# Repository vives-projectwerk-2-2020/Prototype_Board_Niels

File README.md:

# Prototype board with sensors

## Description

In this readme you can find all information about the prototype board with sensors. I made first a test board this board cannot be placed inside the box. This board works perfect with all sensors. The second board i made is made to put inside the box, i also implemented extra pins for the other boards. I also added a extra part to get the SDS011 sensor in sleep mode i will explain this in the info below.

## The nucleo

The central part of my board is the nucleo-L432KC. The STM32 Nucleo-32 board provides an affordable and flexible way for users to try out new concepts and build prototypes with the STM32 microcontroller, choosing from the various combinations of performance, power consumption and features. In the picture below you can see how the nucleo looks like and how the pins are devided. If i talk about pins in the info beneeth you can look on this picture where you can find the pins.

## Shematic of the old board

In this shematic you see in the center of the shematic 2 big blocks the top one is the left side of the nucleo-L432KC. The block below is the right side of the nucleo-L432KC. On the right side from the second nucleo-L432KC block you can see 2 pins they are called JP2 and JP3. These pins were provided for the solar panel board, JP2 is connected with the Vin from the nucleo and JP3 is just the ground. There is also a reset button connected to NRST on the nucleo.

Right below the pins JP2 and JP3 you can see one big connector, this is the connector for connecting the LoRaWAN-antenna board. Pins 1, 8, 9 are connected to the ground, pin 12 is connected with the 3V3 and a capacitor with a value of 100 nF.
Pins 7, 10, 11, 15 are not connected, pin 2 is connected to pin D12 on the nucleo. Pin 3 is connected with D11 on the nucleo, pin 4 is connected with D13 on the nucleo, pin 5 is connected with D0 on the nucleo. Pin 6 is connected with a resistor with a value of 4k7 ohm, this pin is also connected with D1 on the nucleo. Pin 13 is connected with D2 on the nucleo, pin 14 is connected with D3 on the nucleo.

Left from the top block from the nulceo you can see a connector that is called SDS011. This connector has pins so that you connect the SDS011 sensor on it. You can see that pin 1 is not connected this is because the connector from the SDS011 has 5 pins and one is not connected. Pin 2 is connected to 3v3 but this has been changed in the newer shematic because the sensor has to work on 5V, pin 3 is connected to the ground. Pin 4 is connected to D1 on the nucleo and Pin 5 is connected to D0 on the nucleo.

Right from the top block from the nulceo you can see a connector that is called BME280. This connector has female pins so you can put the BME280 sensor on it. Pin 2 is not connected, Pin 1 and 7 are connected to 3V3 and pin 3 and 5 are connected to the ground. Pin 4 is connected to D5 on the nucleo and pin 6 is connected to D4 on the nucleo.

On top of the shematic you can see a big block this is the EEPROM. Pin 2 is connected to the ground and pin 4 is connected to the VCC. Pin 5 is not connected, pin 1 is connected to a resistor with a value of 2k2 ohm to protect the SCL line and is connected tot the D5 on the nucleo. Pin 3 is connected to a resistor with a value of 2k2 ohm to protect the SDA line and is connected with D4 on the nucleo.

## Block diagram old board

Here can you see the block diagram of the old board. This block diagram is a quick summary of what is on my old board.

## Board shematic of the old board

On the top of the board you can see 4 holes this is the VCC of the SDS011 sensor. These holes are were provided so you could erase the line and add more voltage to it from the solar pannel board. These holes were removed on the newest board.

## The print when nothing was soldered

## The print when everything is soldered

## Testing the SDS011 sensor

1. Setup of the sensor.

2. Reading the values in putty.

3. Extra information.
    * The pins are connected on D0 and D1.

## Testing the EEPROM driver

1. Setup of the sensor.

2. Reading out an array in putty.

3. Extra information.
    * While testing i connected the pins to D4 and D5.

## Testing the BME280 sensor

I could not test this sensor because i don't have that sensor at home. I tested it with the fake values from Ladzlo and something was wrong with compiling. But other people tried this sensor and connected it just like how i connected it in my shematic so normally it would work perfectly.

1. Setup of the sensor.

   Connect the sensor in the pins in the red circle shown in the picture below.

2. Extra information.
    * I connected the BME to pins D4 and D5 on the nucleo.

## Testing antenna PCB board

This test has been executed by Laura this pcb works perfectly together with my board all the info about the tests can you find in the github repository from the antenna board.

1. Setup of the boards.

2. Extra information.
    * You can find extra information in the link below.
    * [Link testing LoRaWAN-antenna](https://github.com/vives-projectwerk-2-2020/LoRaWAN-antenna)

## Shematic of the new board

The difference between the old and the new board is that i added extra pins for the battery pcb and also pins for an extra board so that the voltage can go from 3V3 to 5V so that the SDS011 sensor can work well. I also added sleep mode for the SDS011.

Left from the lowest nucleo shematic i added added 3 extra connectors. SV3 is provided so that the solar board can be connected to my board. SV2 are connectors to add the extra print that converts te voltage 3V3 to 5V, we have to do that so that the SDS011 can function well.

Below the SV2 connector there are 2 pins these pins are provided to connect the wires from the batteries to my pcb. In the board you can also see a lot of holes. These holes are provided to connect the pcb with the box, the 2 holes in the center are provided for the batteries you can connect these under the PCB or above.

In the top left of the shematic you can see i added there also extra components. These components are provided so that the SDS011 can go in sleep mode. I connected this to pin D2 on the nucleo, the info about the shematic can you find in the topic "Adding components to the old board so that the SDS011 sensor can go in sleep mode" this will be discussed below.

## Adding components to the old board so that the SDS011 sensor can go in sleep mode

I upgraded the old shematic a bit so that the SDS011 sensor can go in sleep mode. In the picture below you can see the shematic about how to make it.

When the digital output goes high, Q1 is turned on. That pulls down the gate of Q2 low, turning it on.
When the digital output is low, Q1 is held off. R1 then pulls the gate high, turning off Q2.
R1 was chosen to be so high to minimize the current when the device is powered on.

## Block diagram new board

Here can you see the block diagram of the new board. This block diagram is a quick summary of what is on my new board.

## Board shematic of the new board

## The waterproof box

All the boards from the hardware needs to be combined in this waterproof box. In the picture below you can see how we arranged the prints in the box. The grey sensor board is my board, all the other boards will be connected to my board with connectors or with holes in the pcb. I can connect also my pcb to the box. You can see in the picture that the antenna board is far away from the other pcb's. This is because the antenna may not get malfunctions from other boards. The part that is not on the picture but in the box are the batteries. You can add the batteries under my print or add it on top of it with spacers.

## Partlist

* [Female header](https://be.farnell.com/samtec/ssw-107-01-t-s/connector-rcpt-7pos-1row-2-54mm/dp/2667434)
* [Pinheader SDS011](https://be.farnell.com/molex/22-28-4050/connector-header-5pos-1row-2-54mm/dp/2381173)
* [Push button](https://be.farnell.com/c-k-components/pts645sl43-2-lfs/tactile-switch-spst-0-05a-12vdc/dp/2435161)
* [EEPROM](https://be.farnell.com/microchip/24aa64t-i-ot/serial-eeprom-64kbit-400khz-sot/dp/2101260)
* [100 nF capacitor](https://be.farnell.com/avx/02016d104kat2a/cap-0-1-f-6-3v-10-x5r-0201/dp/1657913?st=smd%20capacitor)
* [2k2 ohm resistor](https://be.farnell.com/vishay/crcw06032k20fkeahp/res-2k2-1-0-33w-0603-thick-film/dp/1738909?st=2k2%20smd%20resistor)
* [100k ohm resistor](https://be.farnell.com/vishay/crcw0402100kfked/res-100k-1-0-063w-0402-thick-film/dp/1469671?st=100k%20smd%20resistor)
* [1M ohm resistor](https://be.farnell.com/vishay/crcw04021m00fked/res-1m-1-0-063w-0402-thick-film/dp/1469667?st=1M%20smd%20resistor)
* [4k7 ohm resistor](https://be.farnell.com/vishay/crcw06034k70fkea/res-4k7-1-0-1w-0603-thick-film/dp/1469807?st=4k7%20smd%20resistor)
* [15 pins Female header](https://be.farnell.com/harwin/m20-7821546/connector-rcpt-15pos-2-54mm-1row/dp/3225931)
* [4 pins Female header](https://be.farnell.com/multicomp/2212s-04sg-85/socket-pcb-1-row-4way/dp/1593460)
* [5 pins Female header](https://be.farnell.com/multicomp/2212s-05sg-85/socket-pcb-1-row-5way/dp/1593461)
* [2 pins Male header](https://be.farnell.com/amp-te-connectivity/5-146281-2/board-board-connector-header-2/dp/1792060)
* [Nucleo](https://be.farnell.com/stmicroelectronics/nucleo-l432kc/dev-board-nucleo-32/dp/2580786?scope=partnumberlookahead&ost=NUCLEO-L432KC&searchref=searchlookahead&exaMfpn=true&ddkey=https%3Anl-BE%2FElement14_Belgium%2Fw%2Fsearch)
* [Transistor](https://be.farnell.com/on-semiconductor/mmbt4401lt1g/transistor-npn-sot-23/dp/1459105?st=MMBT4401)
* [Mosfet](https://be.farnell.com/on-semiconductor/ntr4101pt1g/mosfet-p-20v-sot-23/dp/1431303?st=NTR4101PT1G%20P-Channel%20MOSFET)

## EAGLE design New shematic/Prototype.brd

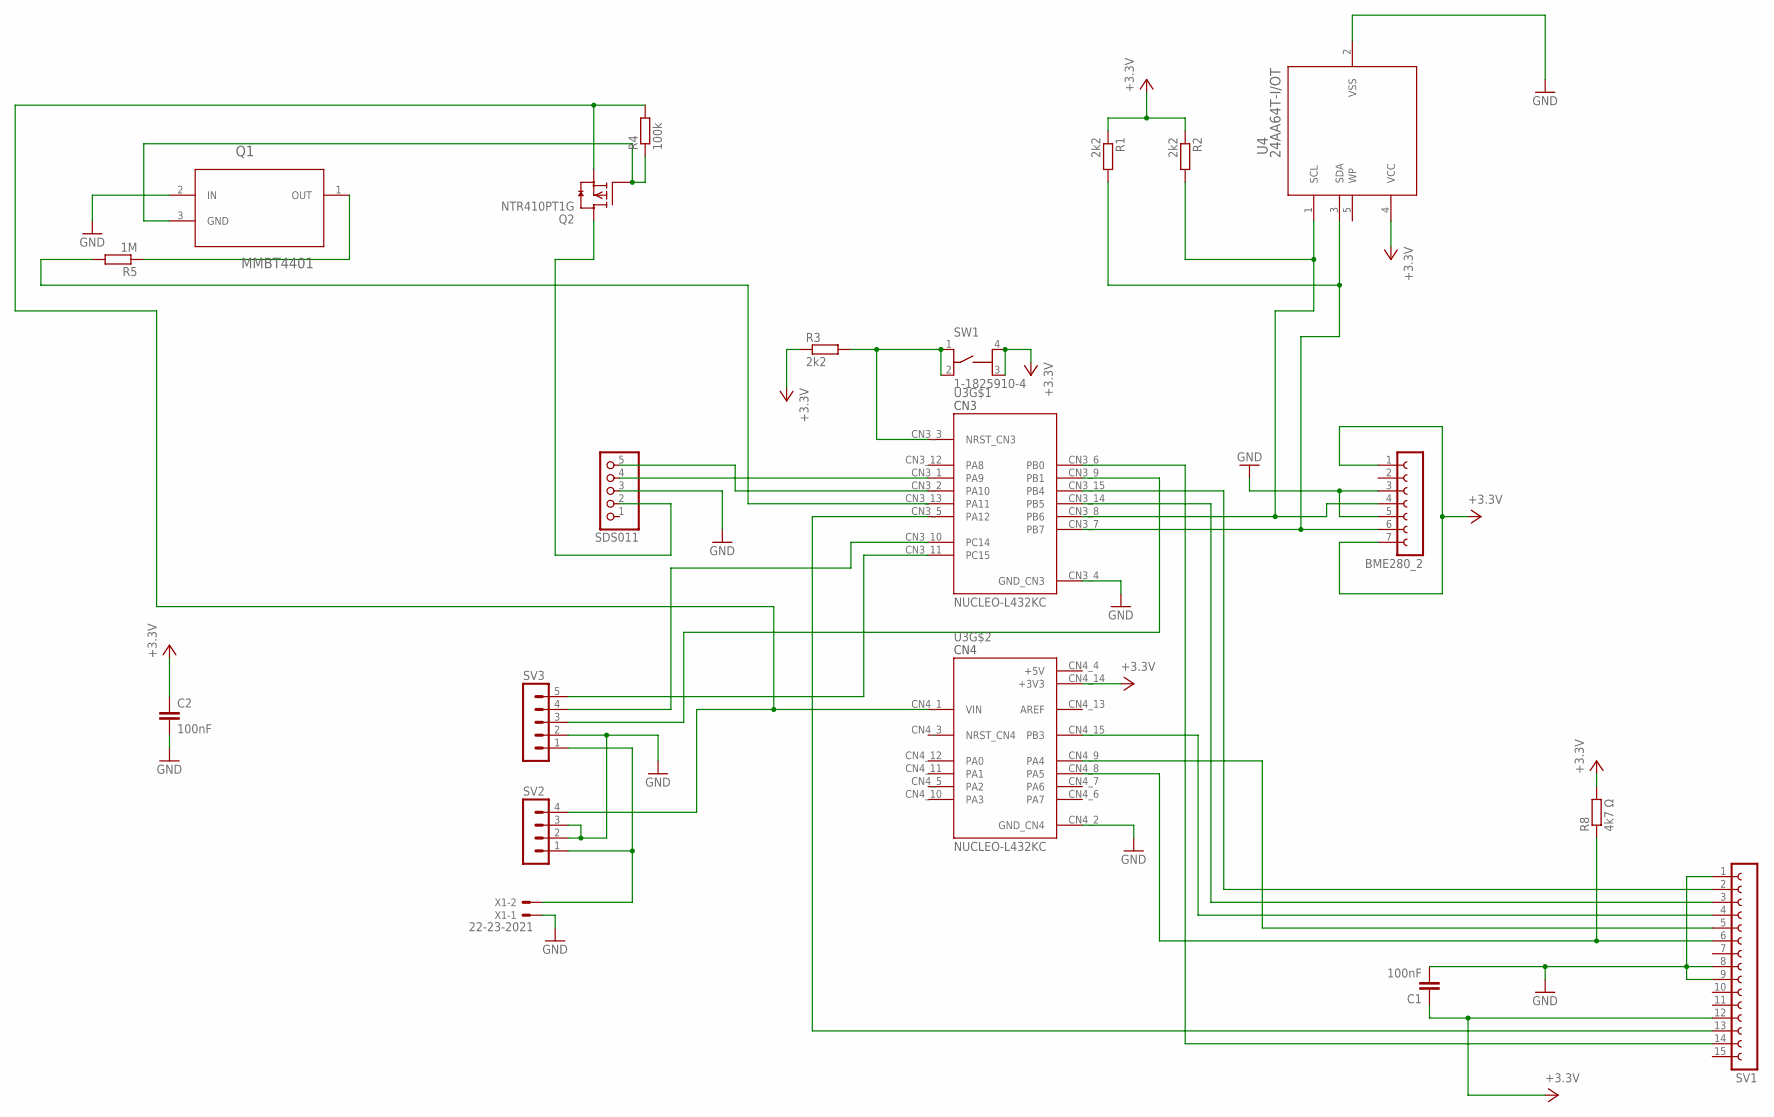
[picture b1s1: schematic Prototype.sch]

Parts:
BME280_2: FE07-1; FE07
C1, C2: 100nF; C0603K
Q1: MMBT4401; SOT95P263X110-3N
Q2: NTR410PT1G; SOT23
R1, R2, R3: 2k2; R1206W
R4: 100k; R1206W
R5: 1M; R1206W
R8: 4k7 Ω; R1206W
SDS011: PINHD-1X5; 1X05
SV1: FE15-1; FE15
SV2: MA04-1
SV3: MA05-1
SW1: 1-1825910-4; TE_1-1825910-4
U3: NUCLEO-L432KC; MODULE_NUCLEO-L432KC
U4: 24AA64T-I/OT; SOT-23-5_MC
X1: 22-23-2021

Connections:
+5V: U3.CN4_4 (+5V)
GND: BME280_2.3, BME280_2.5, C1.2, C2.2, Q1.2 (IN), SDS011.3, SV1.1, SV1.8, SV1.9, SV2.2, SV2.3, SV3.2, U3.CN3_4 (GND_CN3), U3.CN4_2 (GND_CN4), U4.2 (VSS), X1.1
unnamed: SV1.5, U3.CN4_9 (PA4)
unnamed: SDS011.4, U3.CN3_1 (PA9)
unnamed: SV1.14, U3.CN3_6 (PB0)
unnamed: BME280_2.4, R2.2, U3.CN3_8 (PB6), U4.1 (SCL)
unnamed: R3.2, SW1.1, SW1.2, U3.CN3_3 (NRST_CN3)
unnamed: SDS011.5, U3.CN3_2 (PA10)
unnamed: Q1.3 (GND), Q2.1 (G), R4.1
unnamed: Q2.3 (D), SDS011.2
unnamed: SV1.13, U3.CN3_5 (PA12)
unnamed: R8.1, SV1.6, U3.CN4_8 (PA5)
unnamed: SV1.3, U3.CN3_14 (PB5)
unnamed: Q2.2 (S), R4.2, SV2.4, U3.CN4_1 (VIN)
unnamed: SV1.2, U3.CN3_15 (PB4)
unnamed: SV1.4, U3.CN4_15 (PB3)
unnamed: Q1.1 (OUT), R5.1
unnamed: SV2.1, SV3.1, X1.2
unnamed: BME280_2.6, R1.2, U3.CN3_7 (PB7), U4.3 (SDA)
unnamed: SV3.3, U3.CN3_9 (PB1)
unnamed: SV3.4, U3.CN3_10 (PC14)
unnamed: SV3.5, U3.CN3_11 (PC15)
unnamed: R5.2, U3.CN3_13 (PA11)
VCC: BME280_2.1, BME280_2.7, C1.1, C2.1, R1.1, R2.1, R3.1, R8.2, SV1.12, SW1.3, SW1.4, U3.CN4_14 (+3V3), U4.4 (VCC)

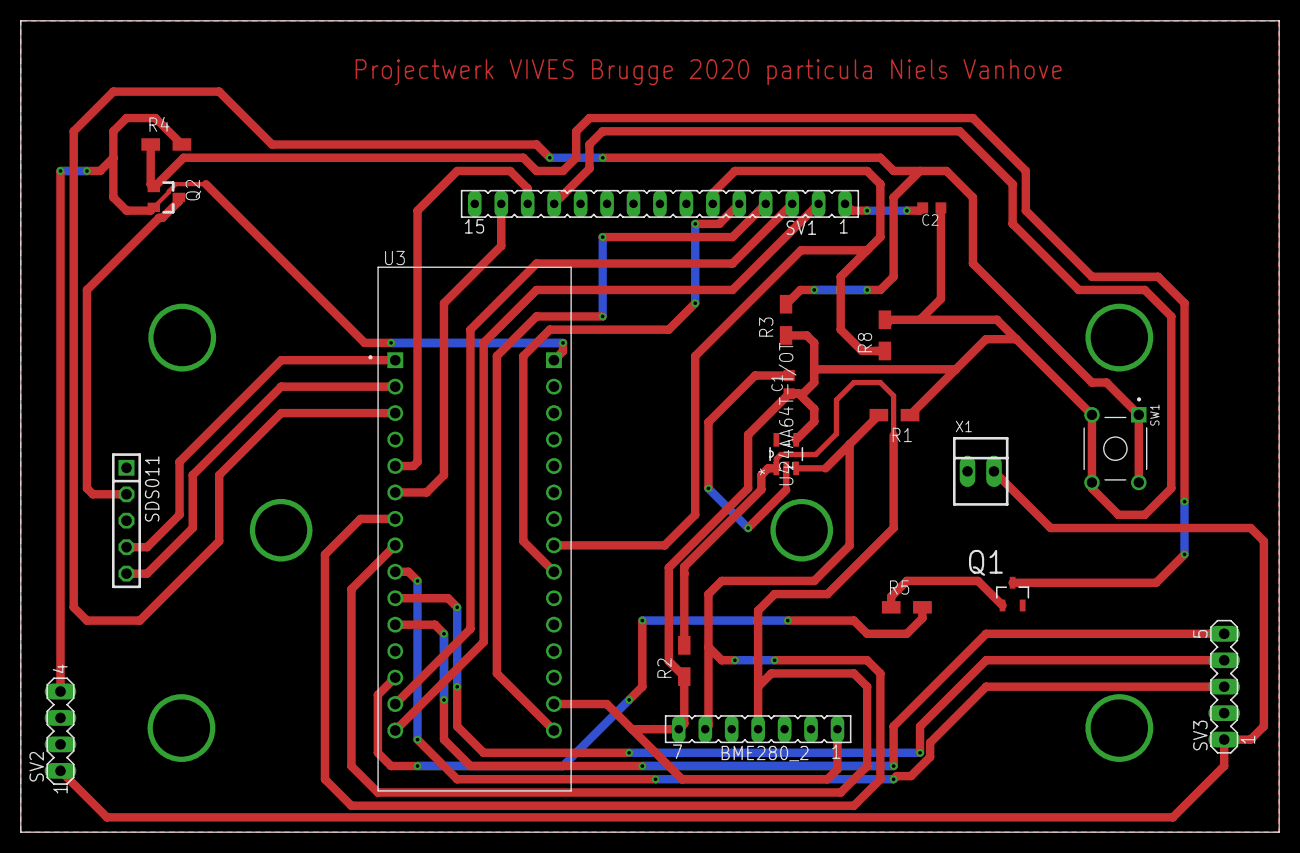
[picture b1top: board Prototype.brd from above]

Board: 2 copper layers, 120.8 x 77.9 mm, 19 parts (0 on the bottom side), 23 nets.

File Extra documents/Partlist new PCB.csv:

Part;Value;Device;Package;Description;Links
BME280_2;;FE07-1;FE07;FEMALE HEADER;https://be.farnell.com/samtec/ssw-107-01-t-s/connector-rcpt-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
C1;100nF;C-EUC0603K;C0603K;CAPACITOR, European symbol;https://be.farnell.com/avx/02016d104kat2a/cap-0-1-f-6-3v-10-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
C2;100nF;C-EUC0603K;C0603K;CAPACITOR, European symbol;https://be.farnell.com/avx/02016d104kat2a/cap-0-1-f-6-3v-10-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
Q1;MMBT4401;LM3480IM3-5.0;SOT95P263X110-3N;Linear Voltage Regulator;https://be.farnell.com/on-semiconductor/mmbt4401lt1g/transis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
Q2;NTR410PT1G;BSS84LT1;SOT23;OnSemi's BSS84LT1 Power MOSFET 130 mA, 50 V RDS(on) = 10;https://be.farnell.com/on-semiconductor/ntr4101pt1g/mosfet-p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
R1;2k2;R-EU_R1206W;R1206W;RESISTOR, European symbol;https://be.farnell.com/vishay/crcw06032k20fkeahp/res-2k2-1-0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
R2;2k2;R-EU_R1206W;R1206W;RESISTOR, European symbol;https://be.farnell.com/vishay/crcw06032k20fkeahp/res-2k2-1-0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
R3;2k2;R-EU_R1206W;R1206W;RESISTOR, European symbol;https://be.farnell.com/vishay/crcw06032k20fkeahp/res-2k2-1-0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
R4;100k;R-EU_R1206W;R1206W;RESISTOR, European symbol;https://be.farnell.com/vishay/crcw0402100kfked/res-100k-1-0-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
R5;1M;R-EU_R1206W;R1206W;RESISTOR, European symbol;https://be.farnell.com/vishay/crcw04021m00fked/res-1m-1-0-06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
R8;4k7 Ω;R-EU_R1206W;R1206W;RESISTOR, European symbol;https://be.farnell.com/vishay/crcw06034k70fkea/res-4k7-1-0-1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
SDS011;;PINHD-1X5;1X05;PIN HEADER;https://be.farnell.com/molex/22-28-4050/connector-header-5po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
SV1;;FE15-1;FE15;FEMALE HEADER;https://be.farnell.com/harwin/m20-7821546/connector-rcpt-15p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
SV2;;MA04-1;MA04-1;PIN HEADER;https://be.farnell.com/multicomp/2212s-04sg-85/socket-pcb-1-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
SV3;;MA05-1;MA05-1;PIN HEADER;https://be.farnell.com/multicomp/2212s-05sg-85/socket-pcb-1-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
SW1;1-1825910-4;1-1825910-4;TE_1-1825910-4;Switch Tactile OFF (ON) ;https://be.farnell.com/c-k-components/pts645sl43-2-lfs/tacti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
U3;NUCLEO-L432KC;NUCLEO-L432KC;MODULE_NUCLEO-L432KC;STM32 Nucleo-32 development board;https://be.farnell.com/microchip/24aa64t-i-ot/serial-eeprom-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
U4;24AA64T-I/OT;24AA64T-I/OT;SOT-23-5_MC;;https://be.farnell.com/stmicroelectronics/nucleo-l432kc/dev-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
X1;22-23-2021;22-23-2021;22-23-2021;".100 (2.54mm) Center Header - 2 Pin""";https://be.farnell.com/amp-te-connectivity/5-146281-2/board-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

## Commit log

2020-04-07 added the shematic to github but this is already in an other github repository
2020-04-07 added 2 pictures of the board
2020-04-07 added pictures by the SDS011
2020-04-07 refactored the images
2020-04-15 tested the EEPROM driver and it worked + added some documentation about the settup and the result in putty
2020-05-08 made new board and shematic
2020-05-12 remaked the pcb board
2020-05-14 refactored the shematic and added components so that sensor can go in sleep
2020-05-16 added old shematic and description to readme
2020-05-16 typed some info about the old shematic
2020-05-16 added board shematic to the readme
2020-05-16 added some extra info to the boards
2020-05-16 added info about the BME sensor
2020-05-16 changed the eeprom picture
2020-05-16 changed the picture name
2020-05-16 trying to fix bug because picture of eeprom is not showing
2020-05-16 added info about the lora wan board
2020-05-16 changed the picture
2020-05-16 adding shematic about sleep mode into readme
2020-05-16 added new shematic to readme
2020-05-16 added new board to readme
2020-05-16 added information about the shematic
2020-05-16 adding extra documents + updating shematic
2020-05-16 added part list to readme
2020-05-16 changed link to antenna project
2020-05-21 added info about the box
2020-05-21 added old block diagram to readme
2020-05-21 added new block diagram to readme
2020-05-21 added picture of the nucleo pins

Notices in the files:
parts and their libraries:
24AA64: COPYRIGHT: Copyright (C) 2018 Accelerated Designs. All rights reserved
